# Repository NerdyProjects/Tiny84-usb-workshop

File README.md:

# Lötworkshop: Bau dir einen kleinen Arduino (oder beginne den Weg dorthin)

Dieses Projekt beschreibt eine kleine Schaltung welche als Bausatz mit verschiedenen Ausbaustufen vorgesehen für absolute Anfänger zum Erlernen von Lötfertigkeiten dienen soll.
Menschen, welche weiter in die Thematik einsteigen möchten, erhalten in der letzten Ausbaustufe ein kleines Arduino-kompatibles Experimentierboard, für das einfach eigene Software geschrieben werden kann.

Diese Anleitung geht hauptsächlich auf Board-spezifische Details ein. Es ist empfohlen, das Löten gemeinsam mit erfahrenen Menschen durchzuführen, welche eine Einführung ins Löten geben und bei Problemen für Hilfestellung da sind.

[Weiter zur Minimalbestückung](bestueck/1_minimum.md)
[Weiter zur 2. Ausbaustufe: Interaktivität](bestueck/2_interactive.md)
[Weiter zur 3. Ausbaustufe: Alternative Stromversorgung](bestueck/3_usb_power.md)
[Weiter zur 4. Ausbaustufe: Arduino](bestueck/4_usb.md)

# (Solder) workshop: Building a tiny, USB capable microcontroller board

## Part list
Start with the absolute minimum and add all the parts you like. If you got this as a workshop kit, your microcontroller should be preprogrammed to do something with just the LED, so you don't need to care about anything else than soldering the components.

If you want to change the code or use a brand new microcontroller, you need some more parts or even a second arduino acting as a programmer. Read on later.
### Absolute minimum
* BT1: Coin cell battery holder, KZH 20-1
* A CR2032 (or similar) 3V Lithium battery to power the board. Put that in when you are done soldering.
* C1: 100 nF THT ceramic capacitor. Optionally, chose a 0805 or 0603 SMD capacitor.
* C2: 4.7µF (or a bit bigger) polarized capacitor (grid 2.5mm). Care: The part has the "-" side marked - that is the filled side on the pcb. The voltage of the capacitor does not matter.
* U2: 14 pin THT IC socket (PDIP-14). This is not necessary but strongly recommended to be able to easily exchange the microcontroller.
* U2: ATTiny84A microcontroller. Choose the one in a 14 pin DIP package.
* D7: 3mm LED: red, green or yellow. Blue/White likely don't work because they need more than 3V.
* R7: 470 ohms resistor - anything from 100-1000 ohms work. It is used to limit the LED current.
* JP1: Either solder a 2 or 3 pin header and use a jumper on pins 2-3 to switch the power on or permanently connect pins 2 and 3 with a piece of wire or tin.

### Some more LEDs
* D6: Another 3mm LED (2)
* R6: Another 470 ohms resistor for the other LED
* D5: Another 3mm LED (3)
* R5: Another 470 ohms resistor

### Some buttons
* SW1 and SW2: 6 or 12mm push buttons

### A buzzer
* A piezo buzzer (7.6mm grid) - SUMMER EPM 121

### Powering the board through USB instead
* JP1: Finally use a 3 pin header here - 1-2 choses USB power, 2-3 choses battery power
* J2: USB B socket - USB BW
* D3 and D4: Any normal diode like 1N4148 to lower the 5V USB voltage a bit.
  * if you don't want to go on and use USB data transfer or external parts, you can use a solder bridge instead, as the board is fine with 5V.

### Allround power supply: 3,5-30 V or USB or Battery
* Remove D3 and D4 and leave them open
* D1, D2: Use any normal diode like 1N4148 so the board uses either an external power or USB - depending on what's available
* U1: LP2950-3.3 a voltage regulator in TO92 package (any other 3.3 V regulator in that package is also fine - 100 mA is enough)

### Changing the microcontrollers software: Get creative!
* D3/D4 need to be in place, alternatively the all-round power supply.
* R1/R2: 68 ohms resistors in series with the USB data lines
* R3: 1.5 kilo ohms resistor that pulls up USB D- to signal the computer that we are a low speed USB device

### Connect some stuff: Pin headers
* Be aware of the voltage external components are compatible with! This board is designed to be operated with 3.3 V as soon as you use USB. Do not connect external 5V input signals!
* Put a 9 pin and a 8 pin header to reach all IO of the microcontroller and put some external hardware to it via jumper wires.
* Put a 4 pin header on the I2C header to connect for example a BME280 temperature sensor shield directly.
  * You likely need R4 and R8 I2C pullup resistors. 2.2 kOhms up to 10 kOhms are probably fine.

### Analog voltage inputs
* Optionally put C3 - another 100 nF ceramic capacitor. This allows better quality analog voltage readings configuring the ADC with external capacitor at Aref.

### Fucked up? 6 pin AVR in system program connector
* solder a 2x3 pin header on the ISP to be able to use a ISP adapter. Alternatively, you can use jumper wires and another Arduino as an ISP adapter, all the ISP pins are available at the other pin headers as well.

## Errata
* Ceramic capacitor footprints are too small for the big capacitors I have
* LED silk screen does not indicate direction (can use Pin1 = square or direction towards ATTiny as GND)
* Experimental area is made from vias that don't have solder mask clearance

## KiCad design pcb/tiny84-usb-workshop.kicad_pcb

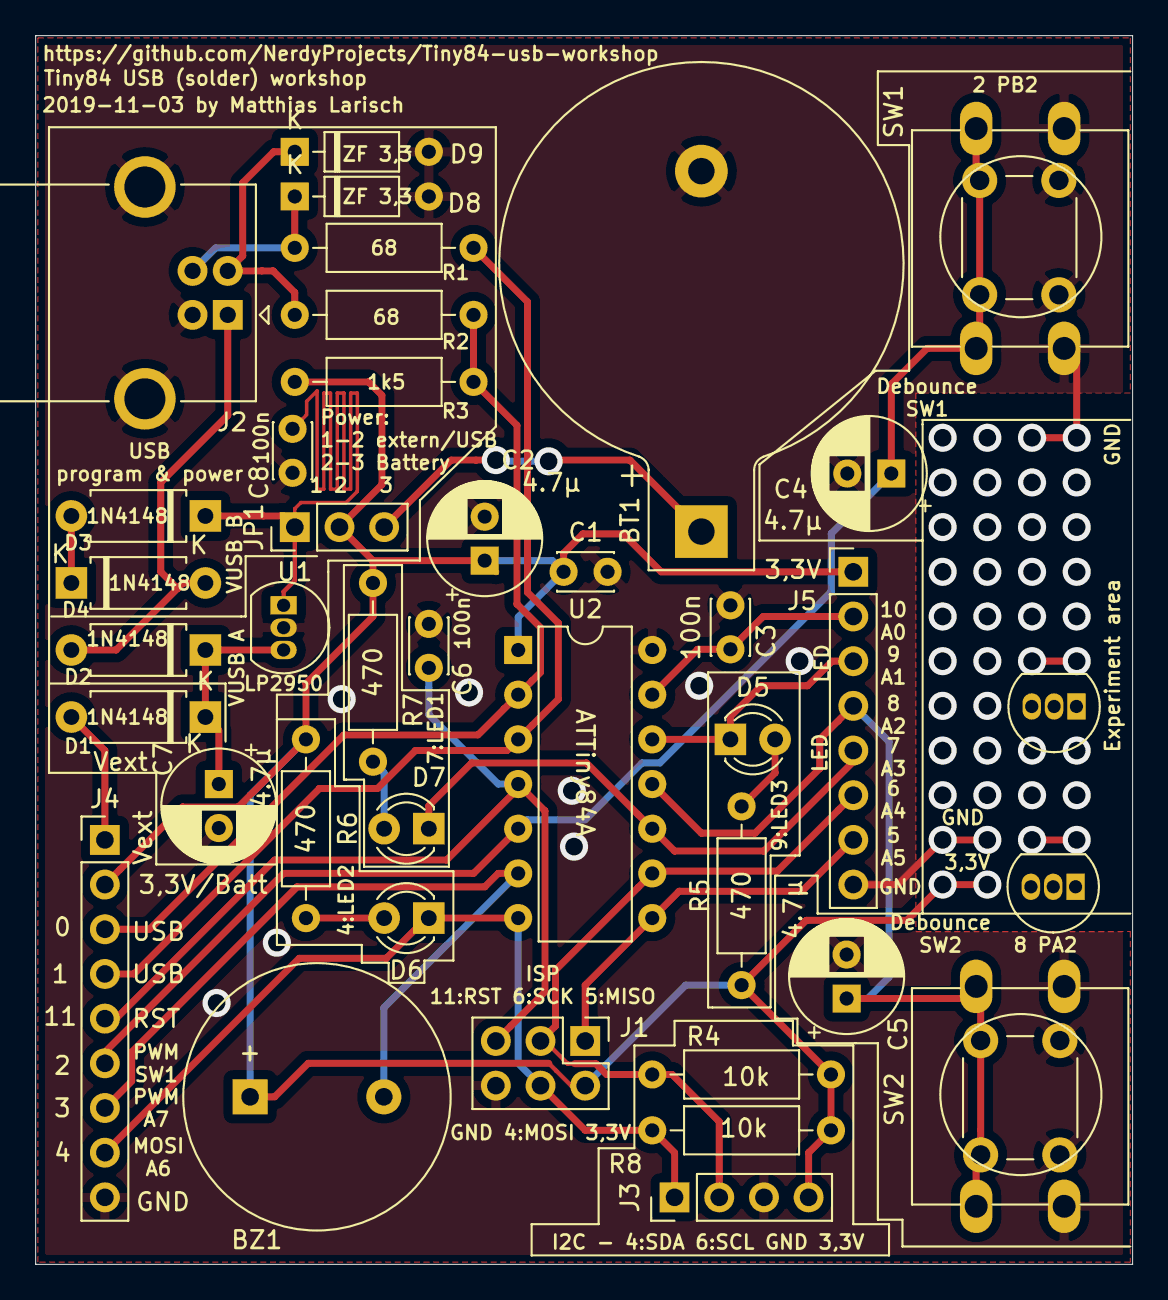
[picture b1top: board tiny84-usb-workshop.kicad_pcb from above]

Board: 2 copper layers, 62.4 x 69.9 mm, 41 parts (0 on the bottom side), 25 nets.

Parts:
BT1: Battery_Cell; BatteryHolder_Keystone_103_1x20mm
BZ1: Buzzer; Buzzer_15x7.5RM7.6
C1, C3, C6, C8: 100n; C_Disc_D3.0mm_W2.0mm_P2.50mm
C2, C4, C5, C7: 4.7µ; CP_Radial_D6.3mm_P2.50mm
D1, D2, D3, D4: 1N4148; D_A-405_P7.62mm_Horizontal
D5: LED3; LED_D3.0mm
D6: LED2; LED_D3.0mm
D7: LED1; LED_D3.0mm
D8, D9: ZF 3,3; D_DO-35_SOD27_P7.62mm_Horizontal
J1: Conn_02x03_Odd_Even; PinHeader_2x03_P2.54mm_Vertical
J2: USB_B; USB_B_OST_USB-B1HSxx_Horizontal
J3: I2C; PinHeader_1x04_P2.54mm_Vertical
J4: Conn_01x09; PinHeader_1x09_P2.54mm_Vertical
J5: Conn_01x08; PinHeader_1x08_P2.54mm_Vertical
JP1: Jumper_3_Open; PinHeader_1x03_P2.54mm_Vertical
Q1, Q2: BC547; TO-92_Inline
R1, R2: 68; R_Axial_DIN0207_L6.3mm_D2.5mm_P10.16mm_Horizontal
R3: 1k5; R_Axial_DIN0207_L6.3mm_D2.5mm_P10.16mm_Horizontal
R4, R8: 10k; R_Axial_DIN0207_L6.3mm_D2.5mm_P10.16mm_Horizontal
R5, R6, R7: 470; R_Axial_DIN0207_L6.3mm_D2.5mm_P10.16mm_Horizontal
SW1: BTN1; SW_PUSH-12mm
SW2: BTN2; SW_PUSH-12mm
SW3, SW4: SW_Push; SW_PUSH_6mm
U1: LP2950-3.3_TO92; TO-92_Inline
U2: ATtiny84A-PU; DIP-14_W7.62mm

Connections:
+3V3: BZ1.1, C1.1, C2.1, J1.2, J3.4, J4.2, J5.1, JP1.2, R3.2, R4.2, R5.1, R6.1, R7.1, R8.2, U2.1
GND: BT1.2, C1.2, C2.2, C3.1, C4.2, C5.2, C6.2, C7.2, C8.2, D8.2, D9.2, J1.6, J2.4, J2.5, J3.3, J4.9, J5.8, SW1.2, SW2.2, SW3.2, SW4.2, U1.2, U2.14
MISO: J1.1, J5.7, U2.8
MOSI: D6.1, J1.4, J3.1, J4.8, R8.1, U2.7
unnamed: BT1.1, JP1.3
unnamed: C7.1, D1.1, D2.1, U1.3
unnamed: C8.1, D3.1, JP1.1, U1.1
unnamed: D2.2, D4.2, J2.1
unnamed: D3.2, D4.1
unnamed: D5.2, R5.2
unnamed: D6.2, R6.2
unnamed: D7.2, R7.2
unnamed: D8.1, J2.3, R1.2
unnamed: D9.1, J2.2, R2.2
PA0: C3.2, J5.2, U2.13
PA1: D5.1, J5.3, U2.12
PA2: C5.1, J5.4, SW2.1, SW4.1, U2.11
PA3: D7.1, J5.5, U2.10
PA7: BZ1.2, J4.7, U2.6
PB2: C4.1, J4.6, SW1.1, SW3.1, U2.5
RESET: C6.1, J1.5, J4.5, U2.4
SCK: J1.3, J3.2, J5.6, R4.1, U2.9
USB_D+: J4.4, R1.1, U2.3
USB_D-: J4.3, R2.1, R3.1, U2.2
VDC: D1.2, J4.1

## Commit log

2019-11-03 initial PCB, WIP
2019-11-03 Readme with part list
2019-11-03 silkscreen adjustments
2019-11-03 finish pcb v1
2019-11-03 fix voltage regulator caps
2019-11-03 Fix missing annotation
2019-11-18 PCB + errata
2019-11-21 WIP demo software
2019-11-27 Update software/schematic version
2019-11-27 more readmes
2019-11-28 Update readme in german
